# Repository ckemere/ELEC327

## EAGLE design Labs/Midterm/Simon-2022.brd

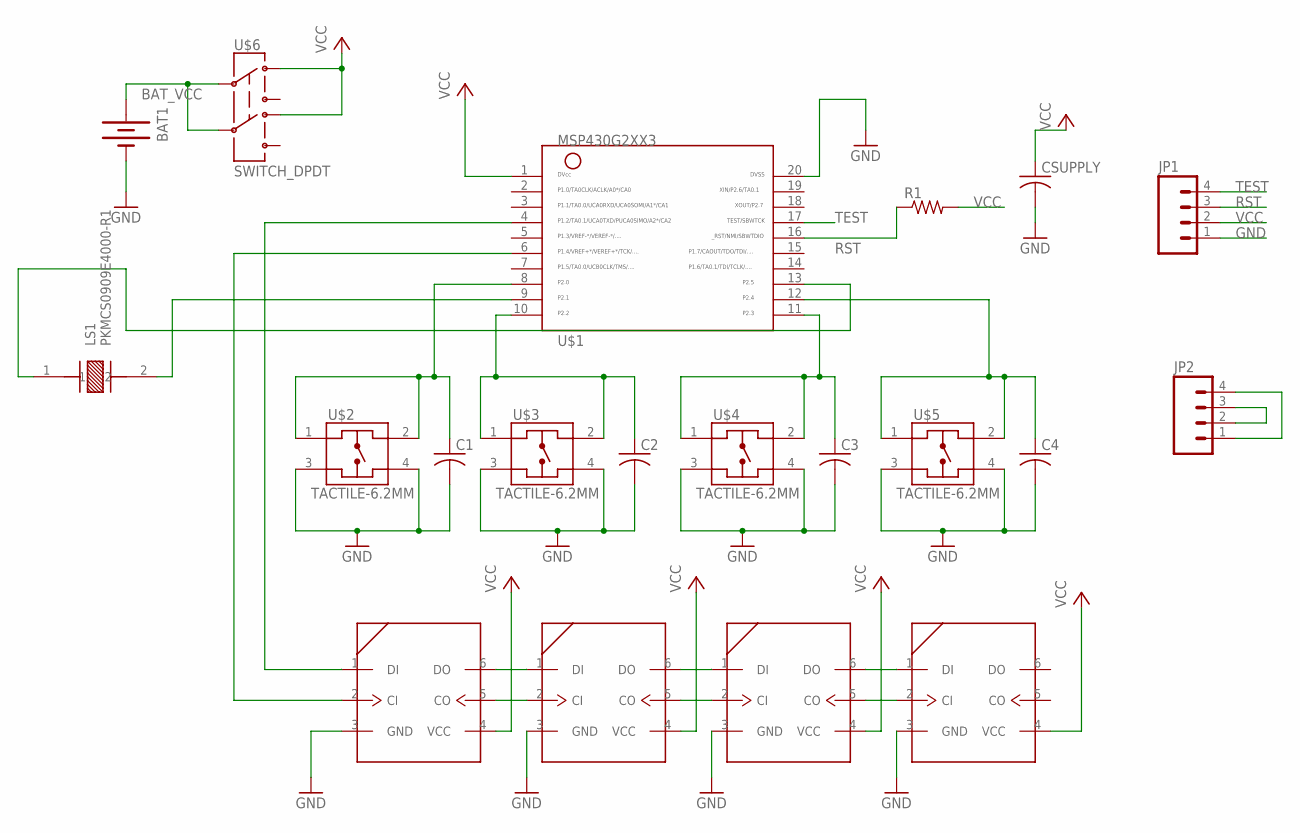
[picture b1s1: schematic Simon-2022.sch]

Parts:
BAT1: BATTERY; BATTERY_PACK_2AA
C1, C2, C3, C4: C-USC1206; C1206
CSUPPLY: C-USC1206; C1206
JP1, JP2: M04LOCK; 1X04_LOCK
LED1, LED2, LED3, LED4: APA102; 5050
LS1: PKMCS0909E4000-R1; XDCR_PKMCS0909E4000-R1
R1: R-US_R1206; R1206
U$1: MSP430G2XX3TSSOP; PW20
U$2, U$3, U$4, U$5: TACTILE-6.2MM; 222_AM
U$6: SWITCH_DPDT; JS_DPDT_TH

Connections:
BAT_VCC: BAT1.3V (+), U$6.2, U$6.5
GND: BAT1.GND (-), C1.2, C2.2, C3.2, C4.2, CSUPPLY.2, JP1.1, LED1.3 (GND), LED2.3 (GND), LED3.3 (GND), LED4.3 (GND), U$1.20, U$2.3 (2), U$2.4, U$3.3 (2), U$3.4, U$4.3 (2), U$4.4, U$5.3 (2), U$5.4
unnamed: LED1.6 (DO), LED2.1 (DI)
unnamed: LED1.5 (CO), LED2.2 (CI)
unnamed: LED2.6 (DO), LED3.1 (DI)
unnamed: LED2.5 (CO), LED3.2 (CI)
unnamed: LED3.6 (DO), LED4.1 (DI)
unnamed: LED3.5 (CO), LED4.2 (CI)
unnamed: LED1.1 (DI), U$1.4
unnamed: LED1.2 (CI), U$1.6
unnamed: C2.1, U$1.10, U$3.1, U$3.2 (3)
unnamed: LS1.2, U$1.9
unnamed: LS1.1, U$1.13
unnamed: C1.1, U$1.8, U$2.1, U$2.2 (3)
unnamed: JP2.1, JP2.4
unnamed: JP2.2, JP2.3
unnamed: C3.1, U$1.11, U$4.1, U$4.2 (3)
unnamed: C4.1, U$1.12, U$5.1, U$5.2 (3)
RST: JP1.3, R1.1, U$1.16
TEST: JP1.4, U$1.17
VCC: CSUPPLY.1, JP1.2, LED1.4 (VCC), LED2.4 (VCC), LED3.4 (VCC), LED4.4 (VCC), R1.2, U$1.1, U$6.1, U$6.4

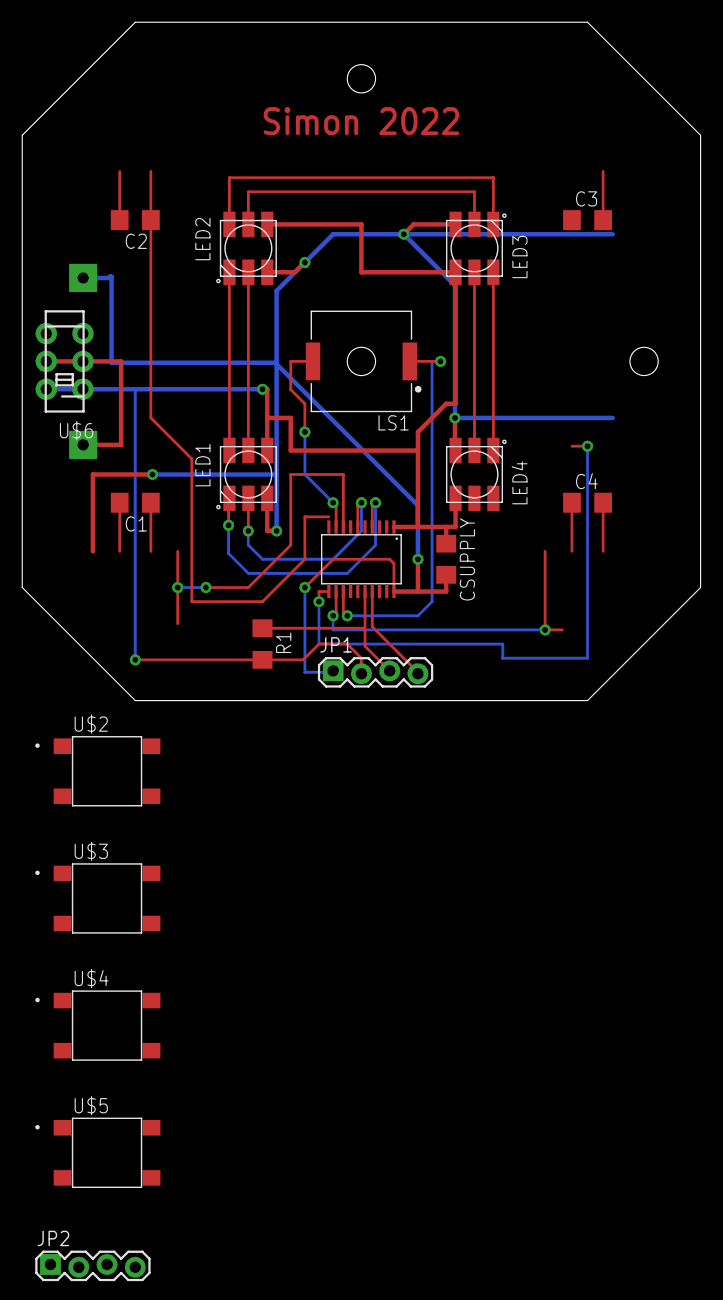
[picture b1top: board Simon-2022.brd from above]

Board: 2 copper layers, 61.0 x 61.0 mm, 20 parts (1 on the bottom side), 21 nets.

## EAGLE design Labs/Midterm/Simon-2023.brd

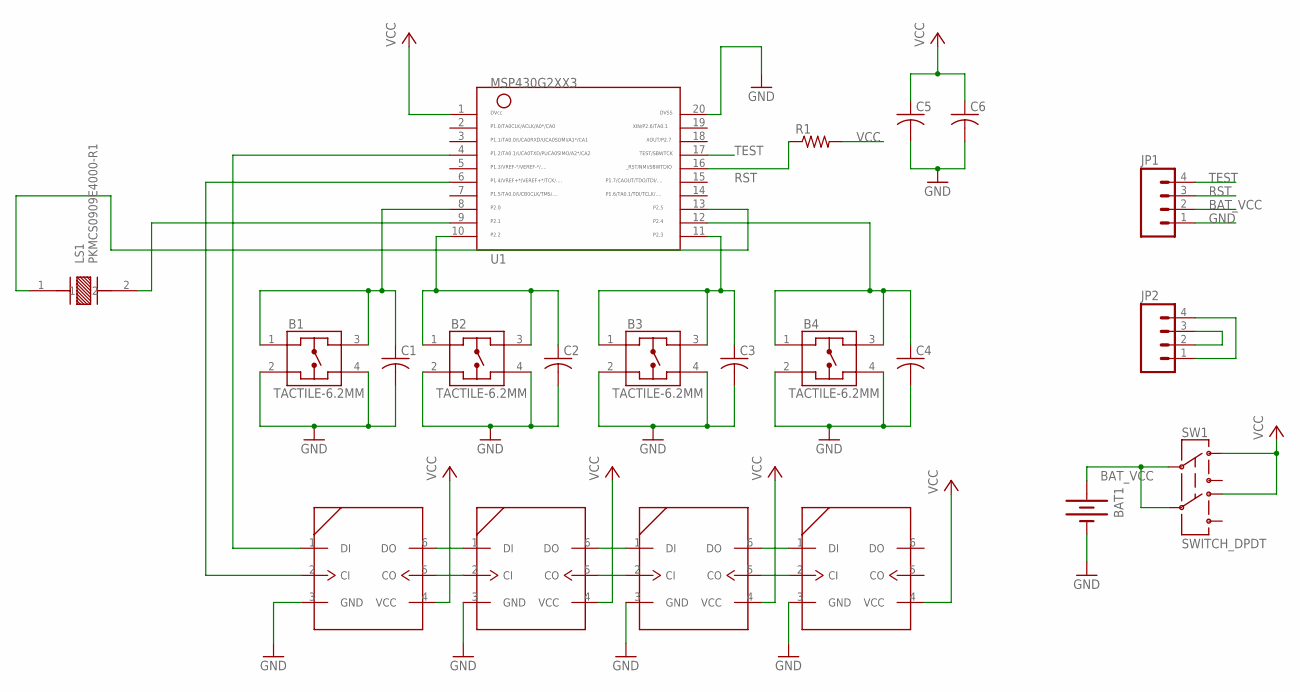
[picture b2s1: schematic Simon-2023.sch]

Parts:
B1, B2, B3, B4: TACTILE-6.2MM; 222_AM
BAT1: BATTERY; BATTERY_PACK_2AA
C1, C2, C3, C4, C6: C-USC0603; C0603
C5: C-USC1206; C1206
JP1, JP2: M04LOCK; 1X04_LOCK
LED1, LED2, LED3, LED4: APA102; 5050
LS1: PKMCS0909E4000-R1; XDCR_PKMCS0909E4000-R1
R1: R-US_R1206; R1206
SW1: SWITCH_DPDT; JS_DPDT_TH
U1: MSP430G2XX3TSSOP; PW20

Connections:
BAT_VCC: BAT1.3V (+), JP1.2, SW1.2, SW1.5
GND: B1.2, B1.4, B2.2, B2.4, B3.2, B3.4, B4.2, B4.4, BAT1.GND (-), C1.2, C2.2, C3.2, C4.2, C5.2, C6.2, JP1.1, LED1.3 (GND), LED2.3 (GND), LED3.3 (GND), LED4.3 (GND), U1.20
unnamed: LED1.6 (DO), LED2.1 (DI)
unnamed: LED1.5 (CO), LED2.2 (CI)
unnamed: LED2.6 (DO), LED3.1 (DI)
unnamed: LED2.5 (CO), LED3.2 (CI)
unnamed: LED3.6 (DO), LED4.1 (DI)
unnamed: LED3.5 (CO), LED4.2 (CI)
unnamed: LED1.1 (DI), U1.4
unnamed: LED1.2 (CI), U1.6
unnamed: B2.1, B2.3, C2.1, U1.10
unnamed: LS1.2, U1.9
unnamed: LS1.1, U1.13
unnamed: B1.1, B1.3, C1.1, U1.8
unnamed: JP2.1, JP2.4
unnamed: JP2.2, JP2.3
unnamed: B3.1, B3.3, C3.1, U1.11
unnamed: B4.1, B4.3, C4.1, U1.12
RST: JP1.3, R1.1, U1.16
TEST: JP1.4, U1.17
VCC: C5.1, C6.1, LED1.4 (VCC), LED2.4 (VCC), LED3.4 (VCC), LED4.4 (VCC), R1.2, SW1.1, SW1.4, U1.1

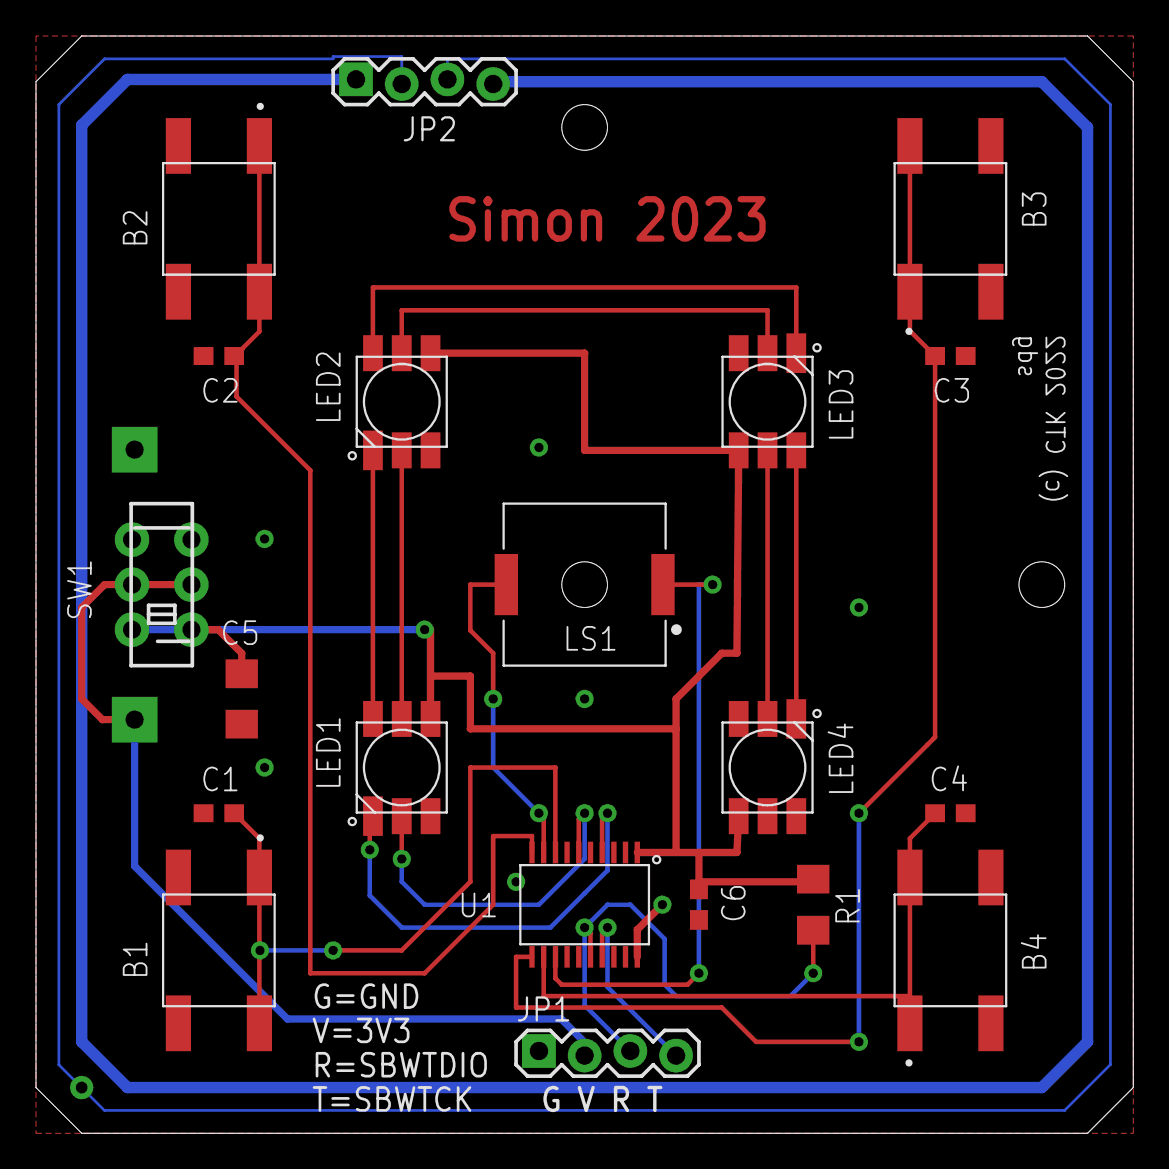
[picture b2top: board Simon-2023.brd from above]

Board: 2 copper layers, 61.0 x 61.0 mm, 21 parts (1 on the bottom side), 21 nets.

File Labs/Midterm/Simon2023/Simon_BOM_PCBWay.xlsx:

|  |  | Simon 2023 50PCS BOM (Sample Bill of Materials)
Item # | *Designator | *Qty | Manufacturer | *Mfg Part # | Description / Value | *Package/Footprint | Type | Your Instructions / Notes
1 | U1 | 1 | TI | MSP430G2333IPW20R | MSP430 CPU16 MSP430G2xx Microcontroller IC 16-Bit 16MHz 4KB (4K x 8) FLASH 20-T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 | 20-TSSOP | SMD
2 | B1, B2, B3, B4 | 4 | CTS Electrocomponents | 222AMVBAR | Tactile Switch SPST-NO Top Actuated Surface Mount | SMT 4P | SMD
3 | LED1, LED2, LED3, LED4 | 4 | American Bright Optoelectronics Corporation | BL-HBGR32L-3-TRB-8 | Addressable Lighting series 1 LED Discrete Serial Red, Green, Blue (RGB) 5.00mm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 | 5050 | SMD
4 | R1 | 1 | Yaego | AC1206FR-0747KL | RES 47.0K OHM 1/8W 1% 1206 SMD | 1206 | SMD | Polarity doesn’t matter
5 | C1, C2, C3, C4 | 4 | Kyocera | 08056D104KAT2A | CAP CER 0.1UF 6.3V 10% X5R 0805 | 0805 | SMD | Polarity doesn’t matter
6 | CSUPPLY | 1 | Kyocera | 1206YD226MAT2A | CAP CER 22UF 16V X5R 20% 1206 | 1206 | SMD | Polarity doesn’t matter
7 | SW1 | 1 | Coiltronics | JS202011CQN | Slide Switch DPDT Through Hole | Thru-hole | thru-hole
8 | JP1 | 1 | Sullins | PRPC004SAAN-RC | Conn Header 4pos 2.54MM | Thru-hole | thru-hole
9 | LS1 | 1 | Mallory Sonalert | AST0940MCTRQ | Piezo Buzzer 9MM | SMD | SMD | Polarity doesn’t matter

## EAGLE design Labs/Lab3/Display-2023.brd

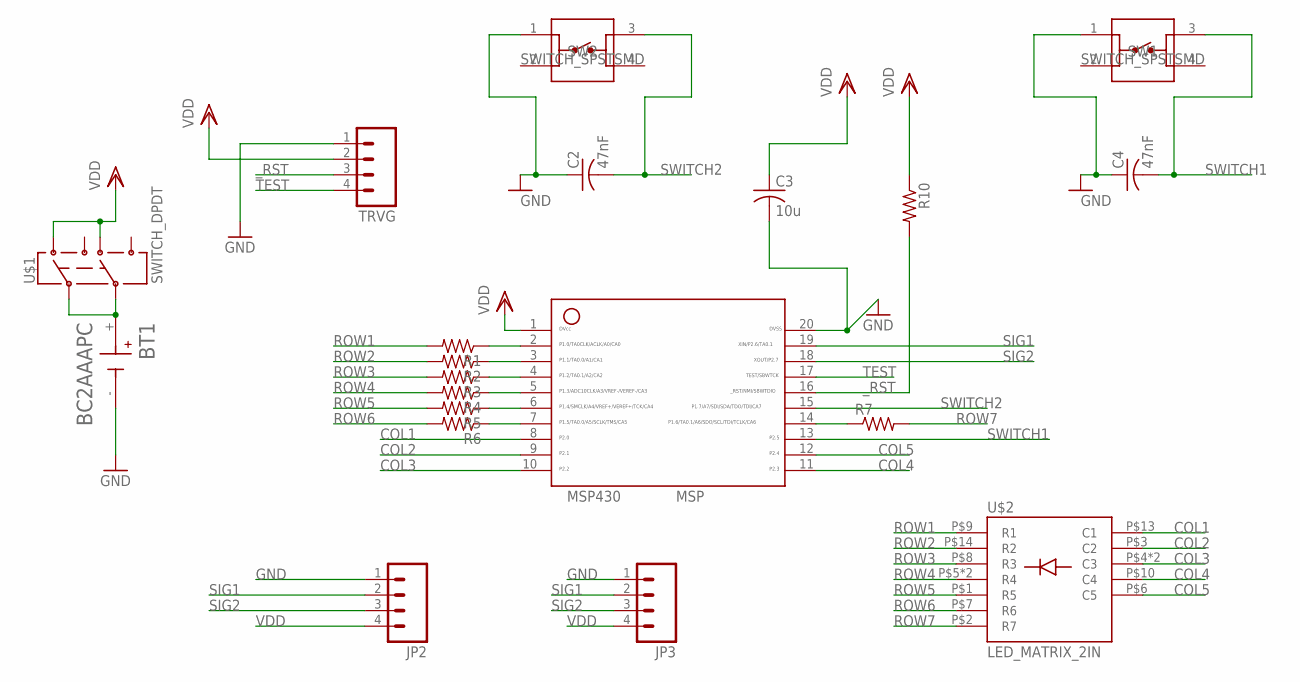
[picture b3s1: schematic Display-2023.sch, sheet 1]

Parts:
BT1: BC2AAAPC; BAT_BC2AAAPC
C2, C4: 47nF; C0603
C3: 10u; C1206
JP2, JP3: M04LOCK; 1X04_LOCK
MSP430: MSP; 20_PIN
R1, R2, R3, R4, R5, R6, R7, R10: R-US_R0402; R0402
SW1, SW2: SWITCH_SPSTSMD; SW_1571563-4
TRVG: M04LOCK; 1X04_LOCK
U$1: SWITCH_DPDT; JS_DPDT_TH
U$2: LED_MATRIX_2IN; LED_MATRIX_5_7

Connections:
COL1: MSP430.8, U$2.P$13 (C1)
COL2: MSP430.9, U$2.P$3 (C2)
COL3: MSP430.10, U$2.P$4 (C3), U$2.P$11 (C3)
COL4: MSP430.11, U$2.P$10 (C4)
COL5: MSP430.12, U$2.P$6 (C5)
GND: BT1.-, C2.1, C3.2, C4.1, JP2.1, JP3.1, MSP430.20, SW1.1, SW2.1, TRVG.1
unnamed: MSP430.14, R7.1
unnamed: MSP430.2, R1.1
unnamed: MSP430.3, R2.1
unnamed: MSP430.4, R3.1
unnamed: MSP430.5, R4.1
unnamed: MSP430.6, R5.1
unnamed: MSP430.7, R6.1
ROW1: R1.2, U$2.P$9 (R1)
ROW2: R2.2, U$2.P$14 (R2)
ROW3: R3.2, U$2.P$8 (R3)
ROW4: R4.2, U$2.P$5 (R4), U$2.P$12 (R4)
ROW5: R5.2, U$2.P$1 (R5)
ROW6: R6.2, U$2.P$7 (R6)
ROW7: R7.2, U$2.P$2 (R7)
SIG1: JP2.2, JP3.2, MSP430.19
SIG2: JP2.3, JP3.3, MSP430.18
SWITCH1: C4.2, MSP430.13, SW1.3
SWITCH2: C2.2, MSP430.15, SW2.3
TEST: MSP430.17, TRVG.4
VBAT: BT1.+, U$1.2, U$1.5
VDD: C3.1, JP2.4, JP3.4, MSP430.1, R10.1, TRVG.2, U$1.1, U$1.4
_RST: MSP430.16, R10.2, TRVG.3

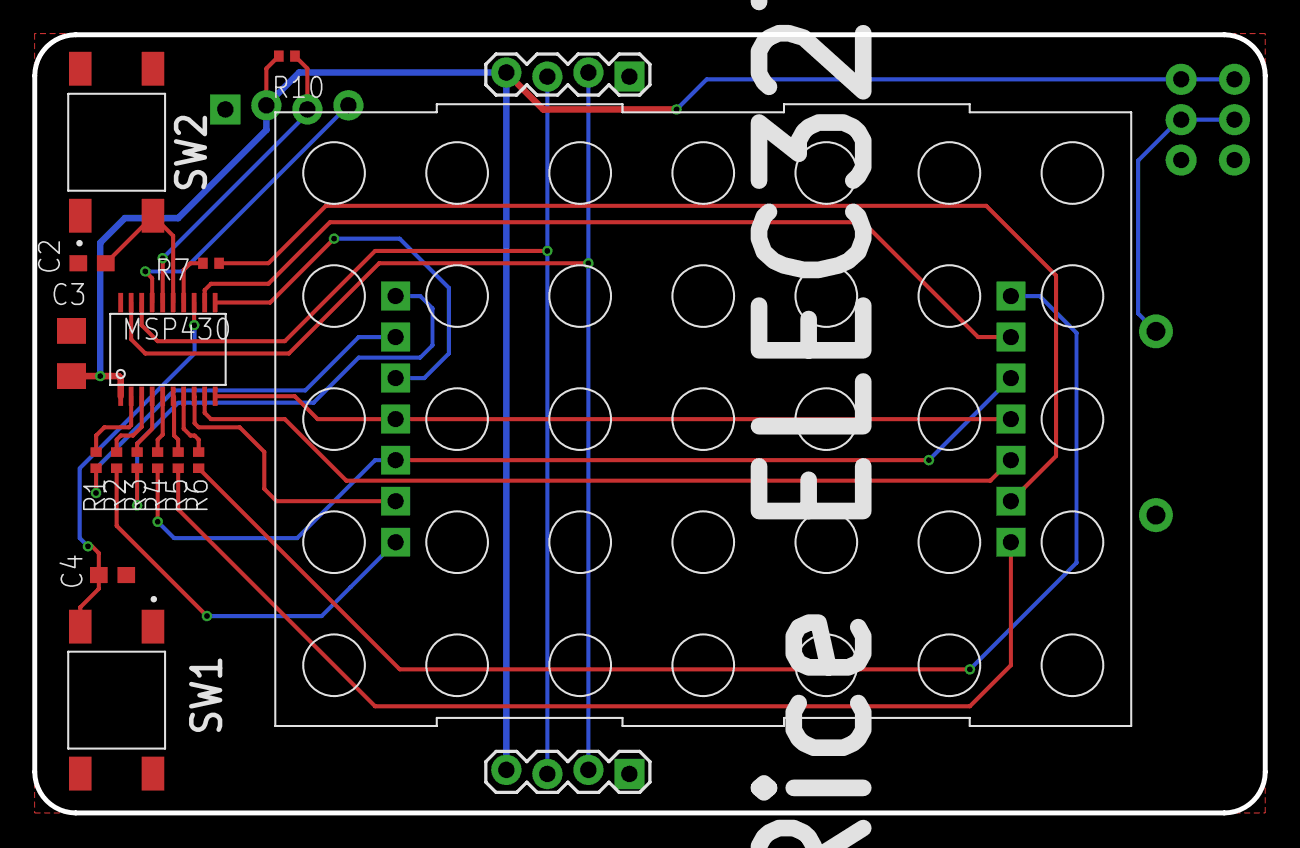
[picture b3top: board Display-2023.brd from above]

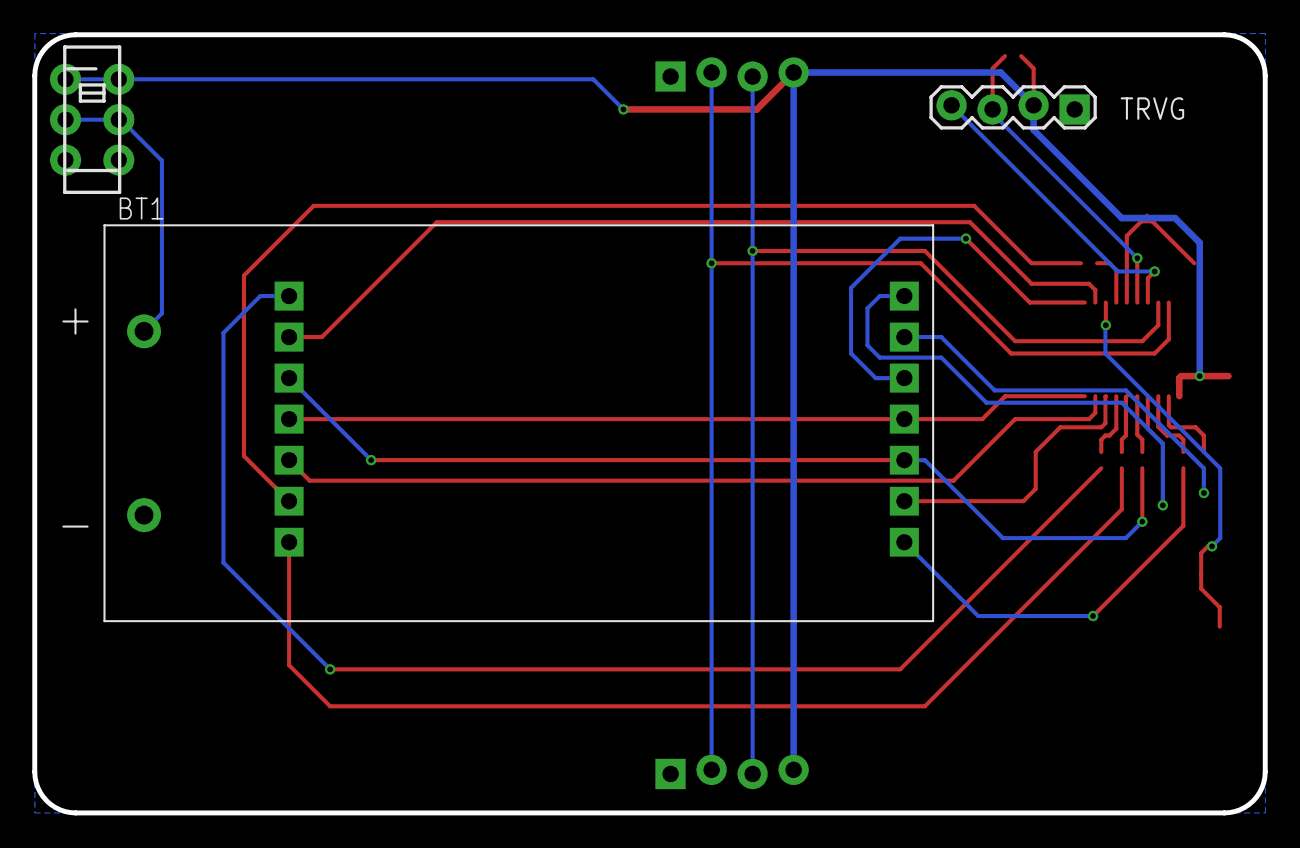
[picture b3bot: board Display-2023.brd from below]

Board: 2 copper layers, 76.2 x 48.2 mm, 20 parts (3 on the bottom side), 28 nets.

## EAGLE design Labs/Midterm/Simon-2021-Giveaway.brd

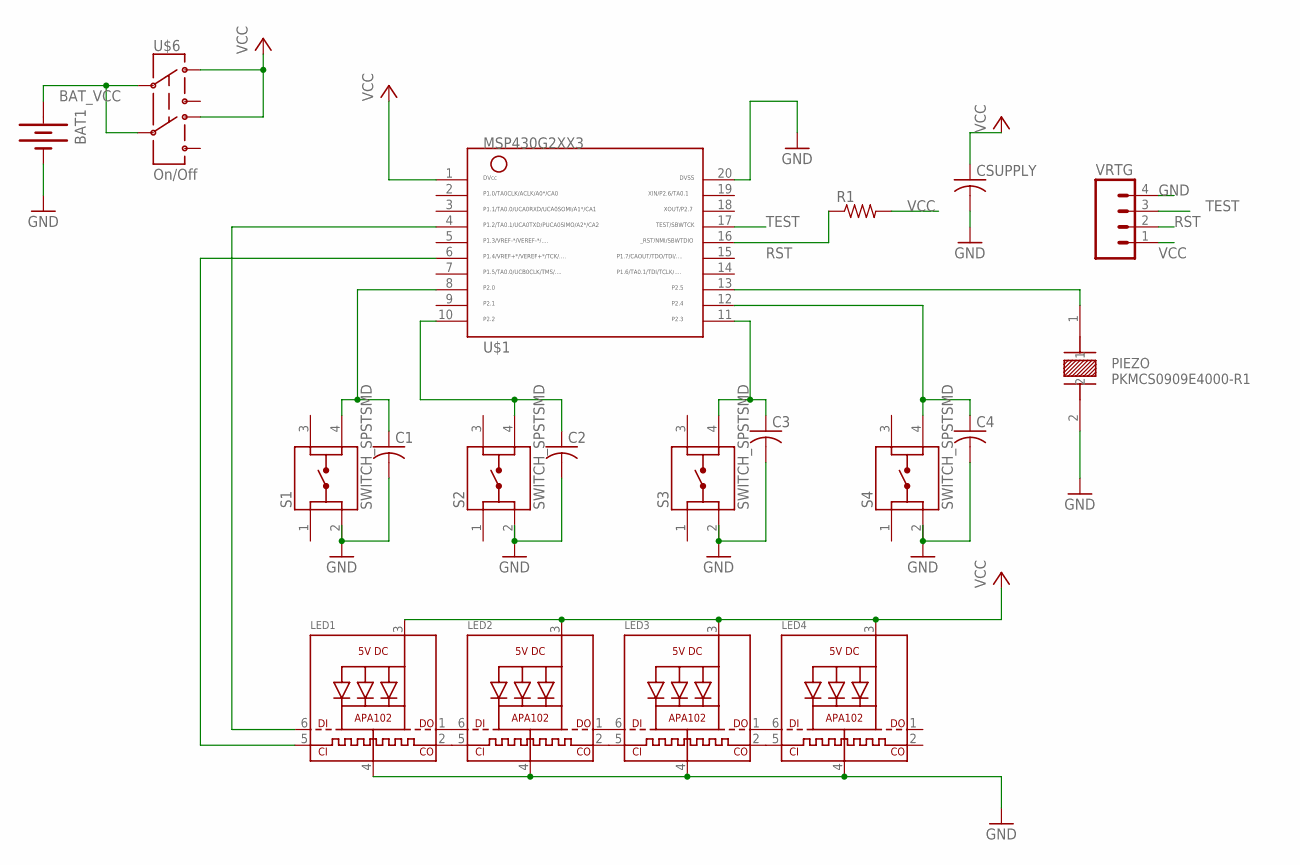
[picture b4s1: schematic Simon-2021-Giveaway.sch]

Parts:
BAT1: BATTERY; BATTERY_PACK_2AA
C1, C2, C3, C4: C-USC1206; C1206
CSUPPLY: C-USC1206; C1206
LED1, LED2, LED3, LED4: APA1022020; APA102_2020
PIEZO: PKMCS0909E4000-R1; XDCR_PKMCS0909E4000-R1
R1: R-US_R1206; R1206
S1, S2, S3, S4: SWITCH_SPSTSMD; SW_1571563-4
U$1: MSP430G2XX3TSSOP; PW20
U$6: On/Off; JS_DPDT_TH
VRTG: M04LOCK; 1X04_LOCK

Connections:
BAT_VCC: BAT1.3V (+), U$6.2, U$6.5
CLK: LED1.5 (CKI), U$1.6
DATA: LED1.6 (DI), U$1.4
GND: BAT1.GND (-), C1.2, C2.2, C3.2, C4.2, CSUPPLY.2, LED1.4 (GND), LED2.4 (GND), LED3.4 (GND), LED4.4 (GND), PIEZO.2, S1.2, S2.2, S3.2, S4.2, U$1.20, VRTG.4
unnamed: PIEZO.1, U$1.13
unnamed: C1.1, S1.4, U$1.8
unnamed: C2.1, S2.4, U$1.10
unnamed: C3.1, S3.4, U$1.11
unnamed: C4.1, S4.4, U$1.12
unnamed: LED1.1 (DO), LED2.6 (DI)
unnamed: LED1.2 (CKO), LED2.5 (CKI)
unnamed: LED2.1 (DO), LED3.6 (DI)
unnamed: LED2.2 (CKO), LED3.5 (CKI)
unnamed: LED3.1 (DO), LED4.6 (DI)
unnamed: LED3.2 (CKO), LED4.5 (CKI)
RST: R1.1, U$1.16, VRTG.2
TEST: U$1.17, VRTG.3
VCC: CSUPPLY.1, LED1.3 (VDD), LED2.3 (VDD), LED3.3 (VDD), LED4.3 (VDD), R1.2, U$1.1, U$6.1, U$6.4, VRTG.1

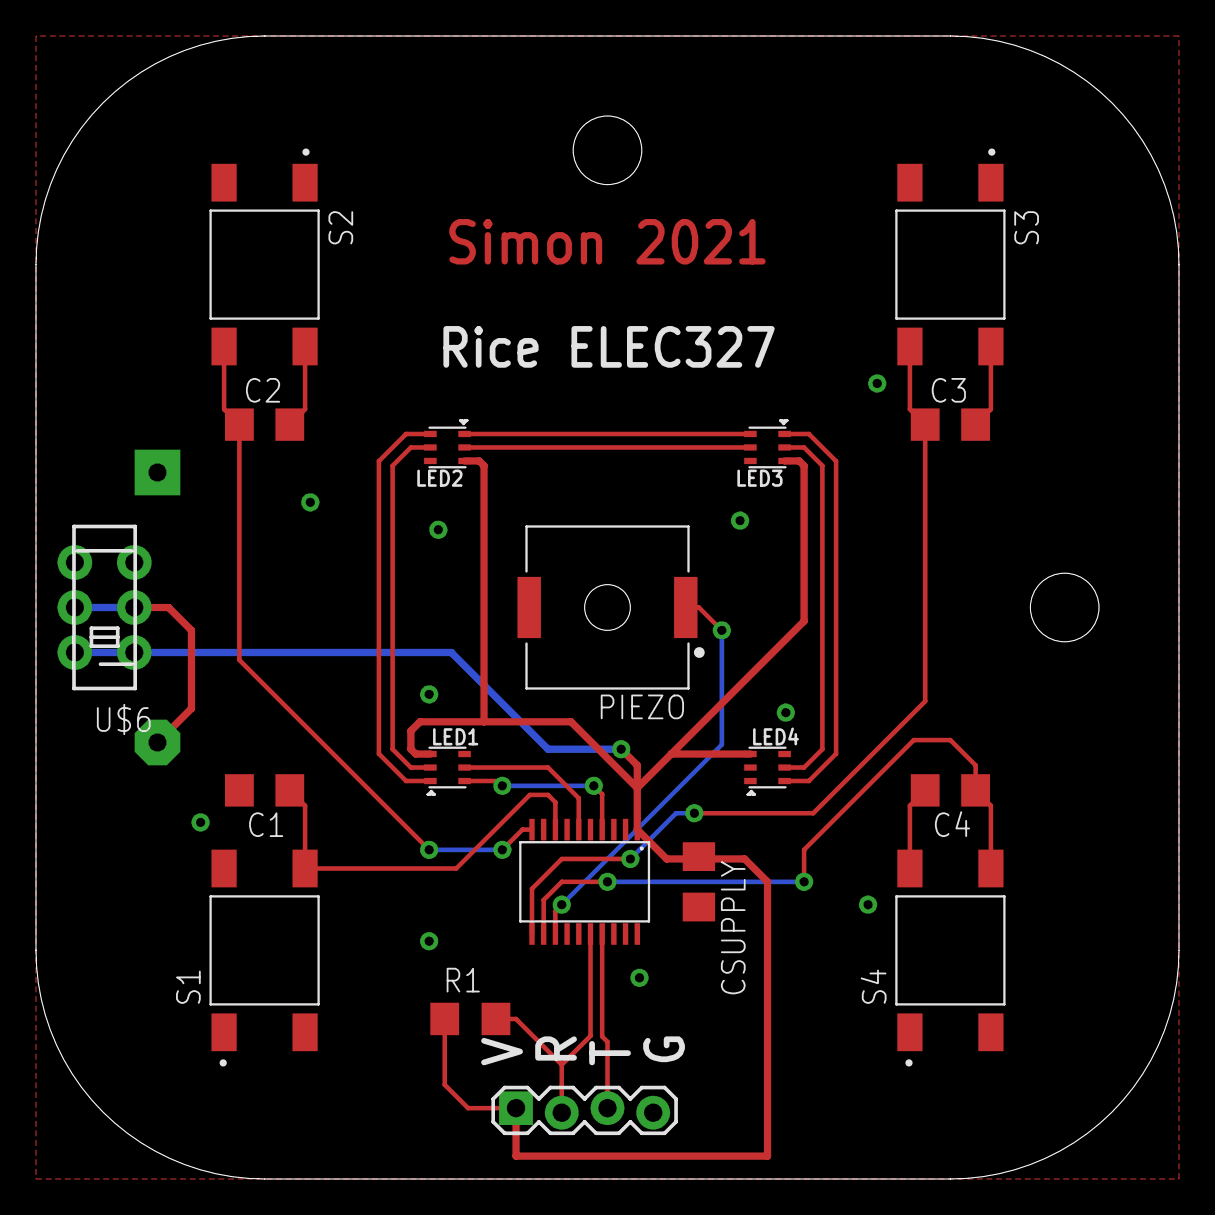
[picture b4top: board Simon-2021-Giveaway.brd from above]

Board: 2 copper layers, 63.5 x 63.5 mm, 19 parts (1 on the bottom side), 18 nets.

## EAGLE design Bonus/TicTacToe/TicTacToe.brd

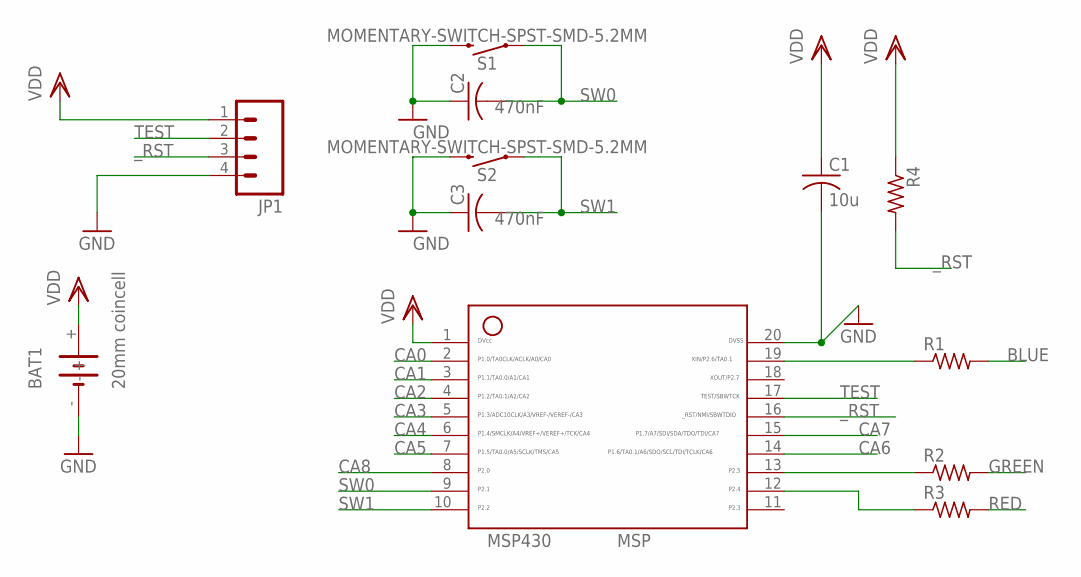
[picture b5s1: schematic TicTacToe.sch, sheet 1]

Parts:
BAT1: 20mm coincell; BAT_1060TR
C1: 10u; C1206
C2, C3: 470nF; C0805
JP1: M04LOCK; 1X04_LOCK
MSP430: MSP; 20_PIN
R1, R2, R3, R4: R-US_R0805; R0805
S1, S2: MOMENTARY-SWITCH-SPST-SMD-5.2MM; TACTILE_SWITCH_SMD_5.2MM

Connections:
BLUE: R1.2; also elsewhere on the board
CA0: MSP430.2; also elsewhere on the board
CA1: MSP430.3; also elsewhere on the board
CA2: MSP430.4; also elsewhere on the board
CA3: MSP430.5; also elsewhere on the board
CA4: MSP430.6; also elsewhere on the board
CA5: MSP430.7; also elsewhere on the board
CA6: MSP430.14; also elsewhere on the board
CA7: MSP430.15; also elsewhere on the board
CA8: MSP430.8; also elsewhere on the board
CB0: MSP430.19, R1.1
GND: BAT1.-, C1.2, C2.1, C3.1, JP1.4, MSP430.20, S1.3 (2), S2.3 (2)
GREEN: R2.2; also elsewhere on the board
unnamed: MSP430.12, R3.1
unnamed: MSP430.13, R2.1
RED: R3.2; also elsewhere on the board
SW0: C2.2, MSP430.9, S1.1
SW1: C3.2, MSP430.10, S2.1
TEST: JP1.2, MSP430.17
VDD: BAT1.+, C1.1, JP1.1, MSP430.1, R4.1
_RST: JP1.3, MSP430.16, R4.2

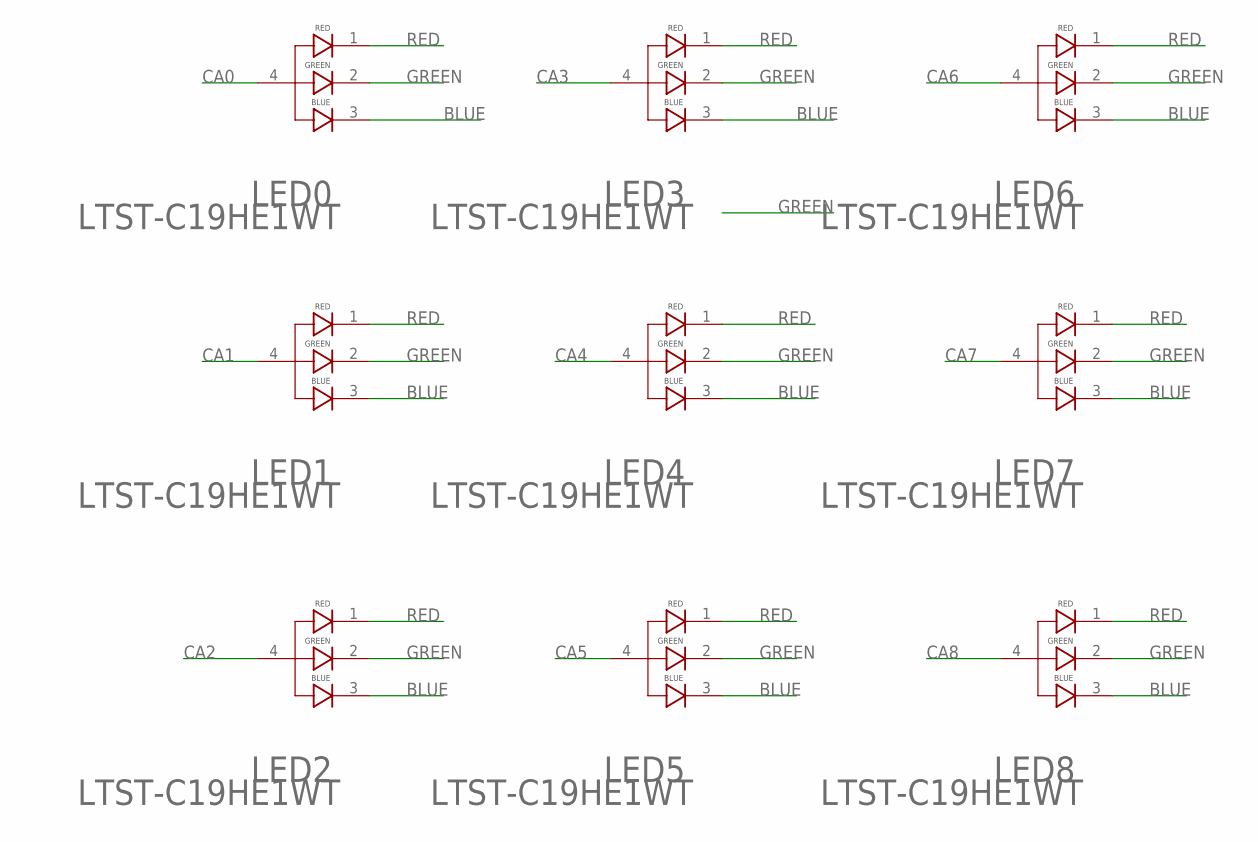
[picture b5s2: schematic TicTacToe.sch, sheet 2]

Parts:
LED0, LED1, LED2, LED3, LED4, LED5, LED6, LED7, LED8: LTST-C19HE1WT; LED_LTST-C19HE1WT

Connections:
BLUE: LED0.3, LED1.3, LED2.3, LED3.3, LED4.3, LED5.3, LED6.3, LED7.3, LED8.3; also elsewhere on the board
CA0: LED0.4; also elsewhere on the board
CA1: LED1.4; also elsewhere on the board
CA2: LED2.4; also elsewhere on the board
CA3: LED3.4; also elsewhere on the board
CA4: LED4.4; also elsewhere on the board
CA5: LED5.4; also elsewhere on the board
CA6: LED6.4; also elsewhere on the board
CA7: LED7.4; also elsewhere on the board
CA8: LED8.4; also elsewhere on the board
GREEN: LED0.2, LED1.2, LED2.2, LED3.2, LED4.2, LED5.2, LED6.2, LED7.2, LED8.2; also elsewhere on the board
RED: LED0.1, LED1.1, LED2.1, LED3.1, LED4.1, LED5.1, LED6.1, LED7.1, LED8.1; also elsewhere on the board

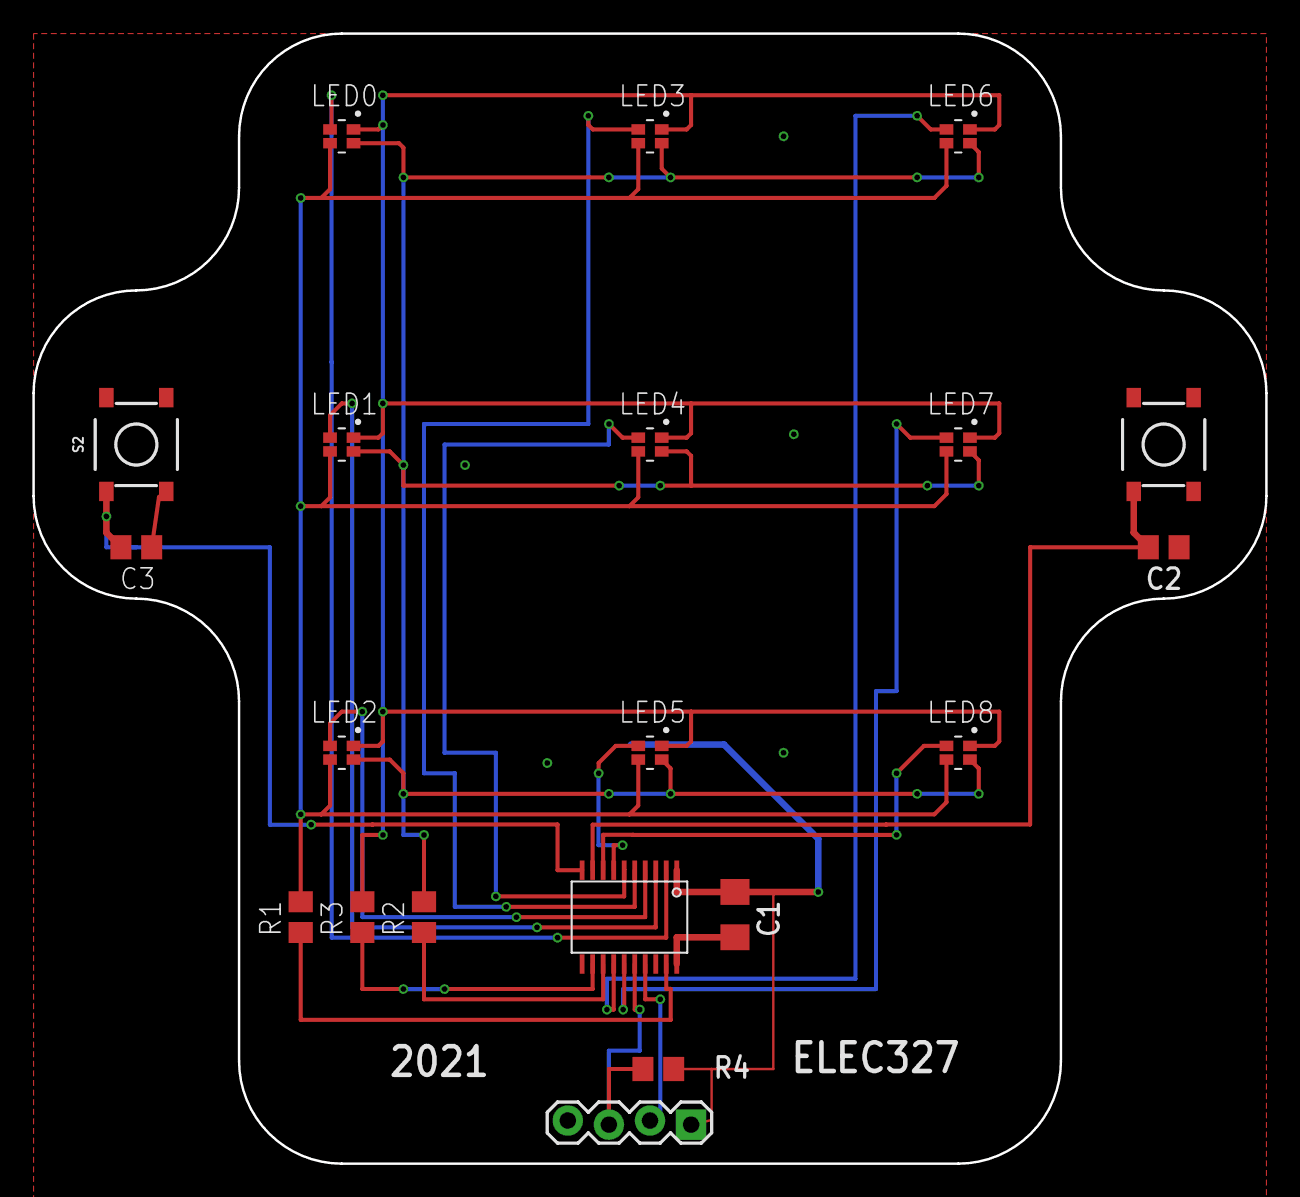
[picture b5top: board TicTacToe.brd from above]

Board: 2 copper layers, 76.2 x 69.8 mm, 21 parts (1 on the bottom side), 21 nets.

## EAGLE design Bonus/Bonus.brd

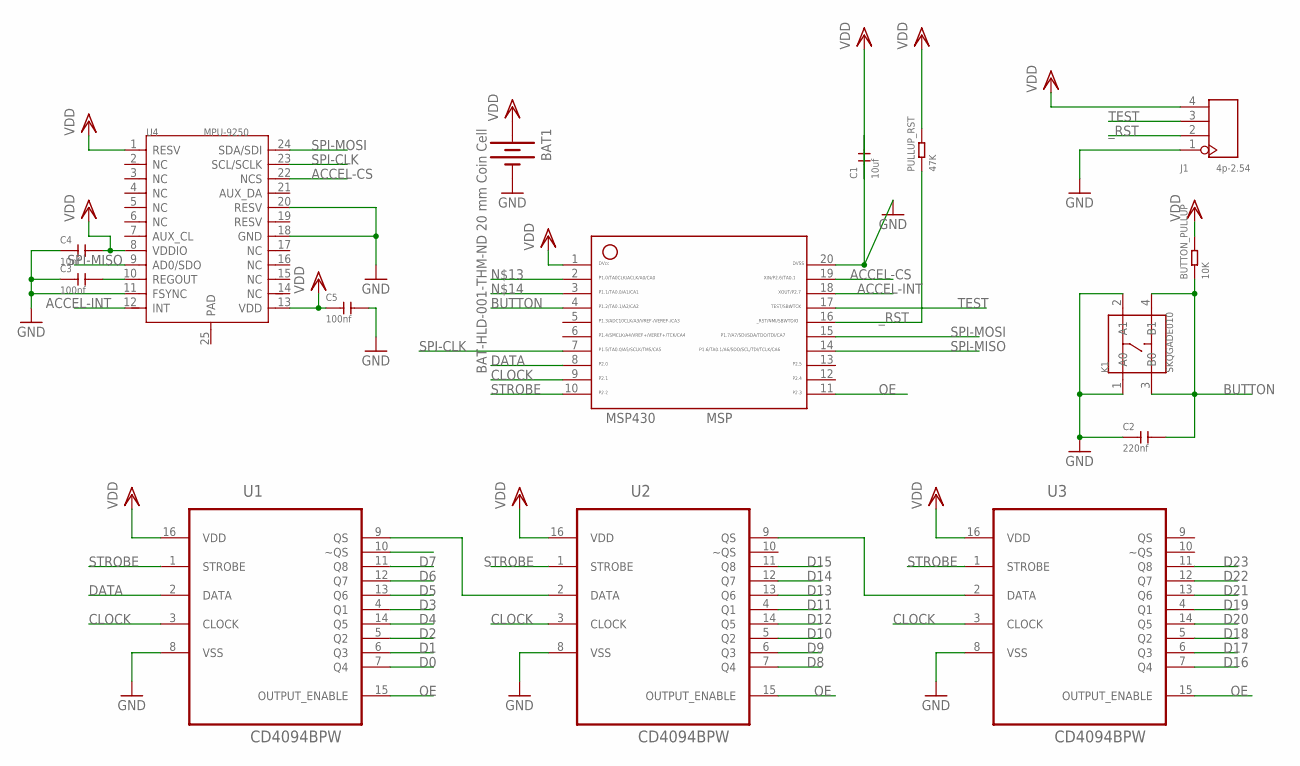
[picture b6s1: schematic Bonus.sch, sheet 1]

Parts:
BAT1: BAT-HLD-001-THM-ND 20 mm Coin Cell; BATTCON_20MM_PTH_COMPACT
BUTTON_PULLUP: 10K; R0603
C1: 10uf; C0805
C2: 220nf; C0603
C3, C5: 100nf; C0402
C4: 10nf; C0402
J1: 4p-2.54; H4-2.54
K1: SKQGADE010; SW4-SMD-5.2X5.2X1.5MM
MSP430: MSP; 20_PIN
PULLUP_RST: 47K; R0603
U1, U2, U3: CD4094BPW; SOP65P640X120-16N
U4: MPU-9250; QFN24G-0.4-3X3MM

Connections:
ACCEL-CS: MSP430.19, U4.22 (NCS)
ACCEL-INT: MSP430.18, U4.12 (INT)
BUTTON: BUTTON_PULLUP.1, C2.2, K1.3 (B0), K1.4 (B1), MSP430.4
CLOCK: MSP430.9, U1.3 (CLOCK), U2.3 (CLOCK), U3.3 (CLOCK)
D0: U1.7 (Q4); also elsewhere on the board
D1: U1.6 (Q3); also elsewhere on the board
D2: U1.5 (Q2); also elsewhere on the board
D3: U1.4 (Q1); also elsewhere on the board
D4: U1.14 (Q5); also elsewhere on the board
D5: U1.13 (Q6); also elsewhere on the board
D6: U1.12 (Q7); also elsewhere on the board
D7: U1.11 (Q8); also elsewhere on the board
D8: U2.7 (Q4); also elsewhere on the board
D9: U2.6 (Q3); also elsewhere on the board
D10: U2.5 (Q2); also elsewhere on the board
D11: U2.4 (Q1); also elsewhere on the board
D12: U2.14 (Q5); also elsewhere on the board
D13: U2.13 (Q6); also elsewhere on the board
D14: U2.12 (Q7); also elsewhere on the board
D15: U2.11 (Q8); also elsewhere on the board
D16: U3.7 (Q4); also elsewhere on the board
D17: U3.6 (Q3); also elsewhere on the board
D18: U3.5 (Q2); also elsewhere on the board
D19: U3.4 (Q1); also elsewhere on the board
D20: U3.14 (Q5); also elsewhere on the board
D21: U3.13 (Q6); also elsewhere on the board
D22: U3.12 (Q7); also elsewhere on the board
D23: U3.11 (Q8); also elsewhere on the board
DATA: MSP430.8, U1.2 (DATA)
GND: BAT1.2 (-), C1.2, C2.1, C3.1, C4.1, C5.2, J1.1, K1.1 (A0), K1.2 (A1), MSP430.20, U1.8 (VSS), U2.8 (VSS), U3.8 (VSS), U4.11 (FSYNC), U4.18 (GND), U4.20 (RESV); also elsewhere on the board
unnamed: U2.9 (QS), U3.2 (DATA)
unnamed: U1.9 (QS), U2.2 (DATA)
unnamed: C3.2, U4.10 (REGOUT)
OE: MSP430.11, U1.15 (OUTPUT_ENABLE), U2.15 (OUTPUT_ENABLE), U3.15 (OUTPUT_ENABLE)
SPI-CLK: MSP430.7, U4.23 (SCL/SCLK)
SPI-MISO: MSP430.14, U4.9 (AD0/SDO)
SPI-MOSI: MSP430.15, U4.24 (SDA/SDI)
STROBE: MSP430.10, U1.1 (STROBE), U2.1 (STROBE), U3.1 (STROBE)
TEST: J1.3, MSP430.17
VDD: BAT1.1 (+), BAT1.3 (+), BAT1.4 (+), BAT1.5 (+), BUTTON_PULLUP.2, C1.1, C4.2, C5.1, J1.4, MSP430.1, PULLUP_RST.2, U1.16 (VDD), U2.16 (VDD), U3.16 (VDD), U4.1 (RESV), U4.8 (VDDIO), U4.13 (VDD)
_RST: J1.2, MSP430.16, PULLUP_RST.1

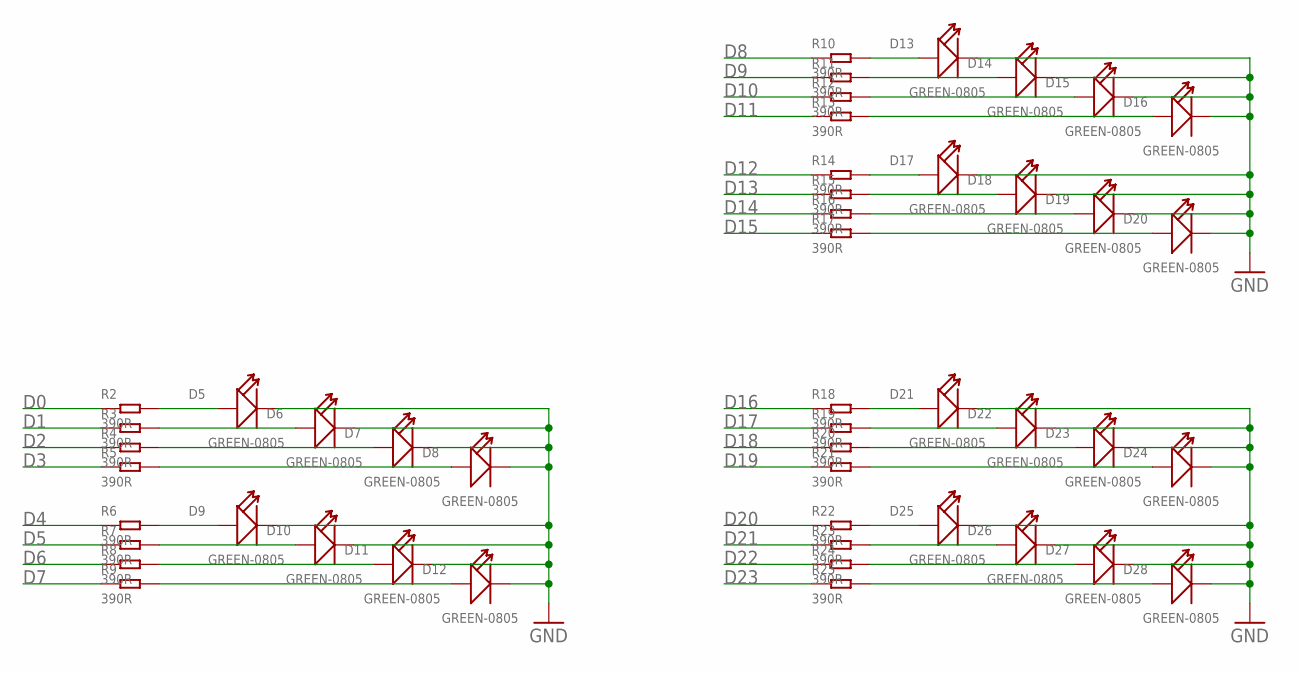
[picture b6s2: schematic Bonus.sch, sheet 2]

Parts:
D5, D6, D7, D8, D9, D10, D11, D12, D13, D14, D15, D16, D17, D18, D19, D20, D21, D22, D23, D24, D25, D26, D27, D28: GREEN-0805; LED-0805
R2, R3, R4, R5, R6, R7, R8, R9, R10, R11, R12, R13, R14, R15, R16, R17, R18, R19, R20, R21, R22, R23, R24, R25: 390R; R0603

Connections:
D0: R2.1; also elsewhere on the board
D1: R3.1; also elsewhere on the board
D2: R4.1; also elsewhere on the board
D3: R5.1; also elsewhere on the board
D4: R6.1; also elsewhere on the board
D5: R7.1; also elsewhere on the board
D6: R8.1; also elsewhere on the board
D7: R9.1; also elsewhere on the board
D8: R10.1; also elsewhere on the board
D9: R11.1; also elsewhere on the board
D10: R12.1; also elsewhere on the board
D11: R13.1; also elsewhere on the board
D12: R14.1; also elsewhere on the board
D13: R15.1; also elsewhere on the board
D14: R16.1; also elsewhere on the board
D15: R17.1; also elsewhere on the board
D16: R18.1; also elsewhere on the board
D17: R19.1; also elsewhere on the board
D18: R20.1; also elsewhere on the board
D19: R21.1; also elsewhere on the board
D20: R22.1; also elsewhere on the board
D21: R23.1; also elsewhere on the board
D22: R24.1; also elsewhere on the board
D23: R25.1; also elsewhere on the board
GND: D5.-, D6.-, D7.-, D8.-, D9.-, D10.-, D11.-, D12.-, D13.-, D14.-, D15.-, D16.-, D17.-, D18.-, D19.-, D20.-, D21.-, D22.-, D23.-, D24.-, D25.-, D26.-, D27.-, D28.-; also elsewhere on the board
unnamed: D5.+, R2.2
unnamed: D6.+, R3.2
unnamed: D7.+, R4.2
unnamed: D8.+, R5.2
unnamed: D9.+, R6.2
unnamed: D10.+, R7.2
unnamed: D11.+, R8.2
unnamed: D12.+, R9.2
unnamed: D13.+, R10.2
unnamed: D14.+, R11.2
unnamed: D15.+, R12.2
unnamed: D16.+, R13.2
unnamed: D17.+, R14.2
unnamed: D18.+, R15.2
unnamed: D19.+, R16.2
unnamed: D20.+, R17.2
unnamed: D21.+, R18.2
unnamed: D22.+, R19.2
unnamed: D23.+, R20.2
unnamed: D24.+, R21.2
unnamed: D25.+, R22.2
unnamed: D26.+, R23.2
unnamed: D27.+, R24.2
unnamed: D28.+, R25.2

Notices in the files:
Bonus/Bonus.brd:
(c) 2019
parts and their libraries:
SparkFun-Switches-Modified: Licensing: Creative Commons ShareAlike 4.0 International - https://creativecommons.org/licenses/by-sa/4.0
SparkFun: Licensing: CC v3.0 Share-Alike You are welcome to use this library for commercial purposes.
